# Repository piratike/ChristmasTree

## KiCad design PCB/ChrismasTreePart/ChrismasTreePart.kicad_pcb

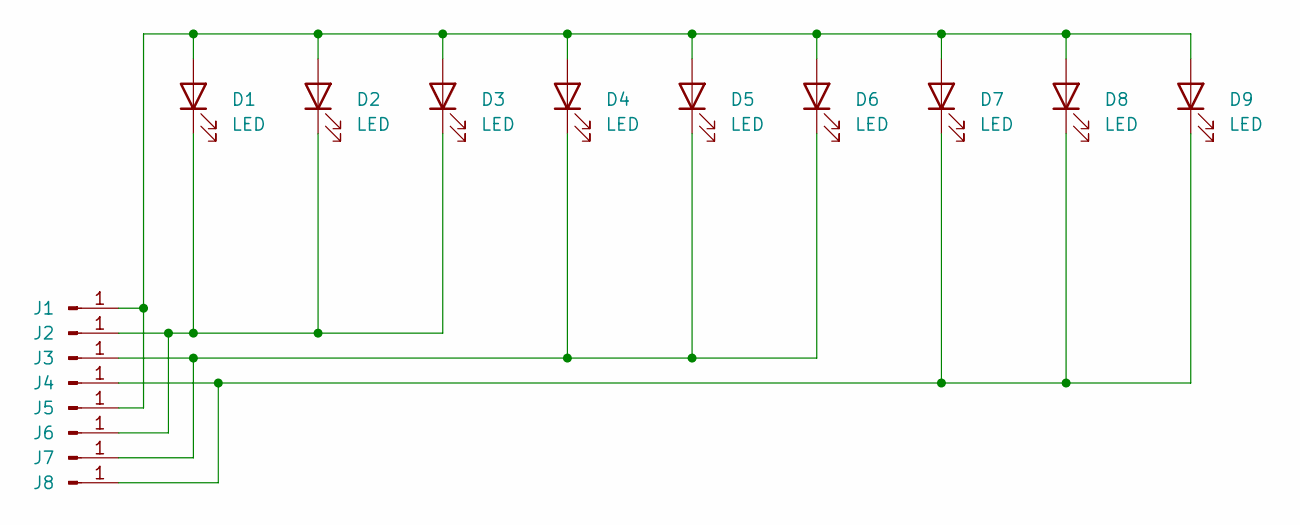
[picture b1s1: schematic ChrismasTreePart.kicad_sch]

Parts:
D1, D2, D3, D4, D5, D6, D7, D8, D9: LED; LED_D5.0mm
J1, J2, J3, J4, J5, J6, J7, J8: Conn_01x01_Pin; TestPoint_Pad_2.0x2.0mm

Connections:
unnamed: D1.2 (A), D2.2 (A), D3.2 (A), D4.2 (A), D5.2 (A), D6.2 (A), D7.2 (A), D8.2 (A), D9.2 (A), J1.1, J5.1
unnamed: D1.1 (K), D2.1 (K), D3.1 (K), J2.1, J6.1
unnamed: D4.1 (K), D5.1 (K), D6.1 (K), J3.1, J7.1
unnamed: D7.1 (K), D8.1 (K), D9.1 (K), J4.1, J8.1

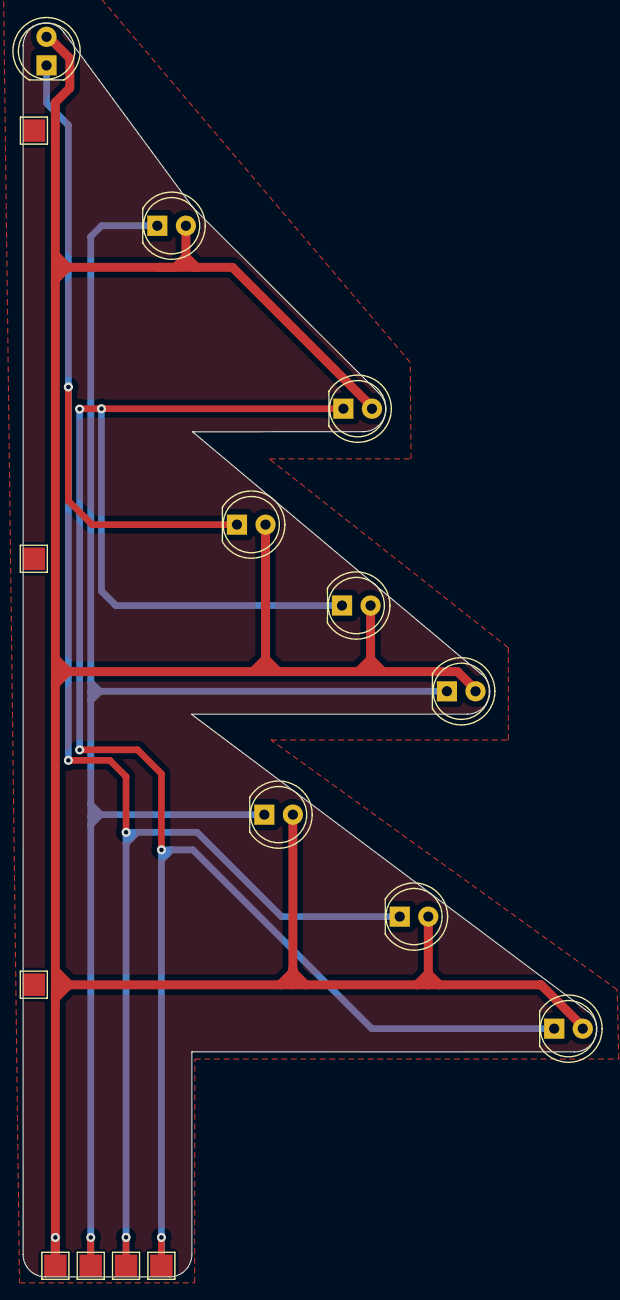
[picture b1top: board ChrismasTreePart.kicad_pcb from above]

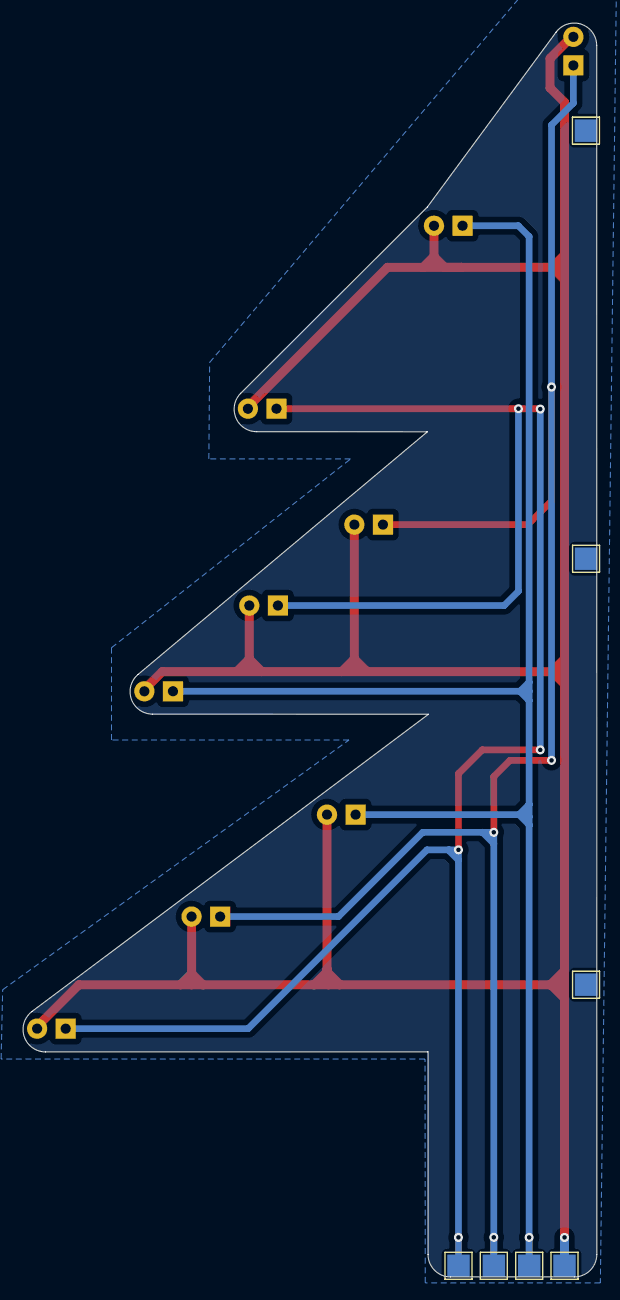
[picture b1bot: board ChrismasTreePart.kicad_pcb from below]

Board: 2 copper layers, 51.0 x 111.4 mm, 17 parts (4 on the bottom side), 4 nets.

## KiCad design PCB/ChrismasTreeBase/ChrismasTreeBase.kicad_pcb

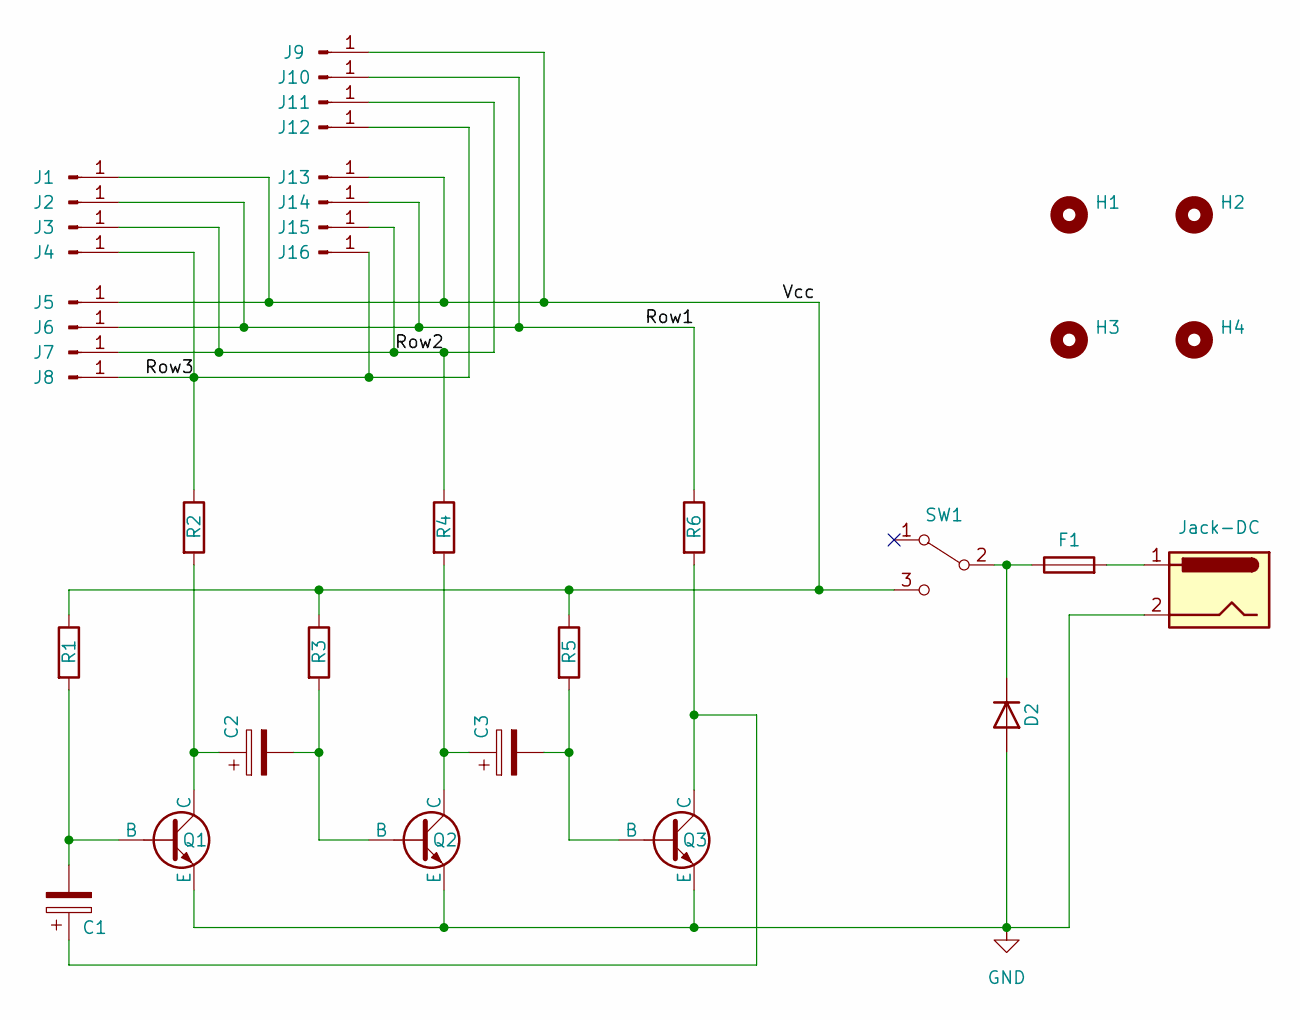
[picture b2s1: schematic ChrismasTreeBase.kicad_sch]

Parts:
C1, C2, C3: 22u; CP_Radial_D6.3mm_P2.50mm
D2: D; D_A-405_P10.16mm_Horizontal
F1: 500mA; Fuse_Bourns_MF-RG300
H1, H2, H3, H4: MountingHole_3.2mm_M3
J1, J2, J3, J4, J5, J6, J7, J8, J9, J10, J11, J12, J13, J14, J15, J16: Conn_01x01_Pin; TestPoint_Pad_2.0x2.0mm
J17: Jack-DC; BarrelJack_Horizontal
Q1, Q2, Q3: NPN; TO-92_Inline_Wide
R1, R3, R5: 10k; R_Axial_DIN0207_L6.3mm_D2.5mm_P10.16mm_Horizontal
R2, R4, R6: R; R_Axial_DIN0207_L6.3mm_D2.5mm_P10.16mm_Horizontal
SW1: SW_SPDT; SW_CuK_OS102011MA1QN1_SPDT_Angled

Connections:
/Row1: J2.1, J6.1, J10.1, J14.1, R6.1
/Row2: J3.1, J7.1, J11.1, J15.1, R4.1
/Row3: J4.1, J8.1, J12.1, J16.1, R2.1
/Vcc: J1.1, J5.1, J9.1, J13.1, R1.1, R3.1, R5.1, SW1.3 (C)
GND: D2.2 (A), J17.2, Q1.3 (E), Q2.3 (E), Q3.3 (E)
unnamed: D2.1 (K), F1.1, SW1.2 (B)
unnamed: F1.2, J17.1
unnamed: C1.2, Q1.2 (B), R1.2
unnamed: C2.1, Q1.1 (C), R2.2
unnamed: C2.2, Q2.2 (B), R3.2
unnamed: C3.1, Q2.1 (C), R4.2
unnamed: C3.2, Q3.2 (B), R5.2
unnamed: C1.1, Q3.1 (C), R6.2

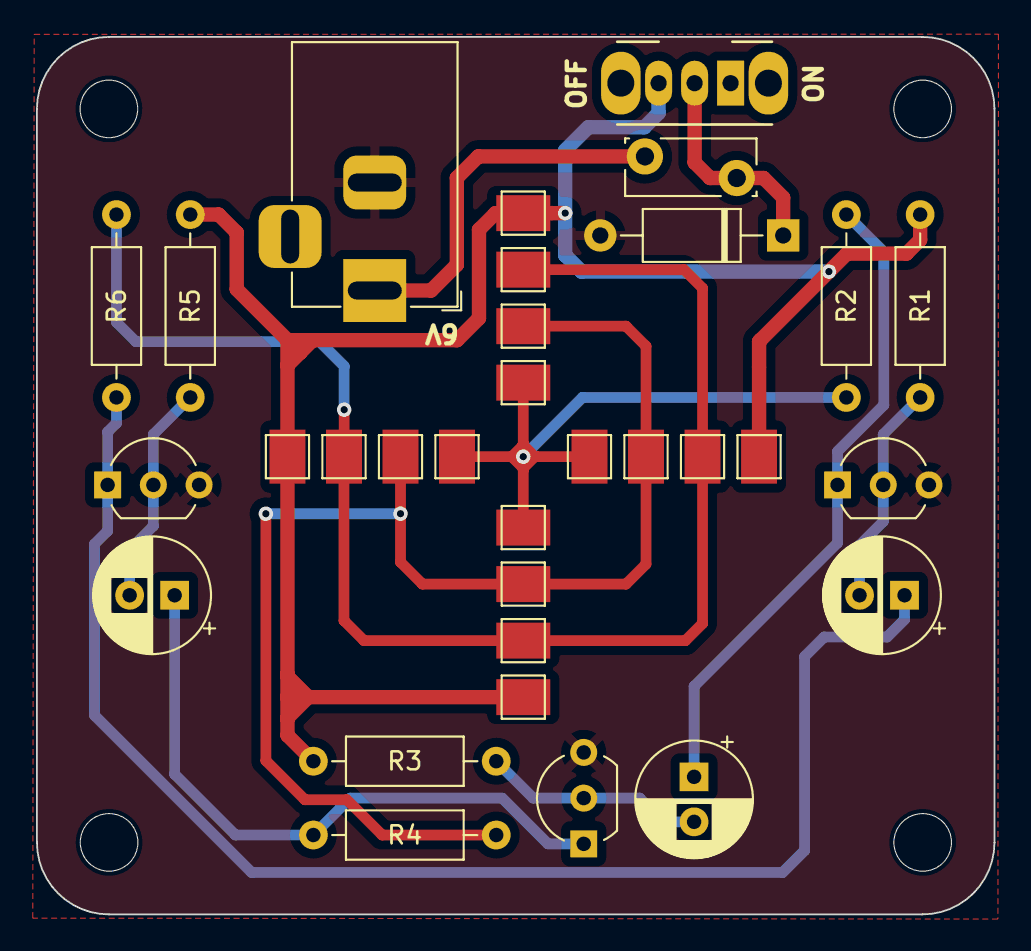
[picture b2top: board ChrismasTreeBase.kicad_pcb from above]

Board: 2 copper layers, 53.2 x 48.8 mm, 36 parts (0 on the bottom side), 13 nets.

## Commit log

2024-02-24 Created christmas tree PCB. It needs two different boards to work.
